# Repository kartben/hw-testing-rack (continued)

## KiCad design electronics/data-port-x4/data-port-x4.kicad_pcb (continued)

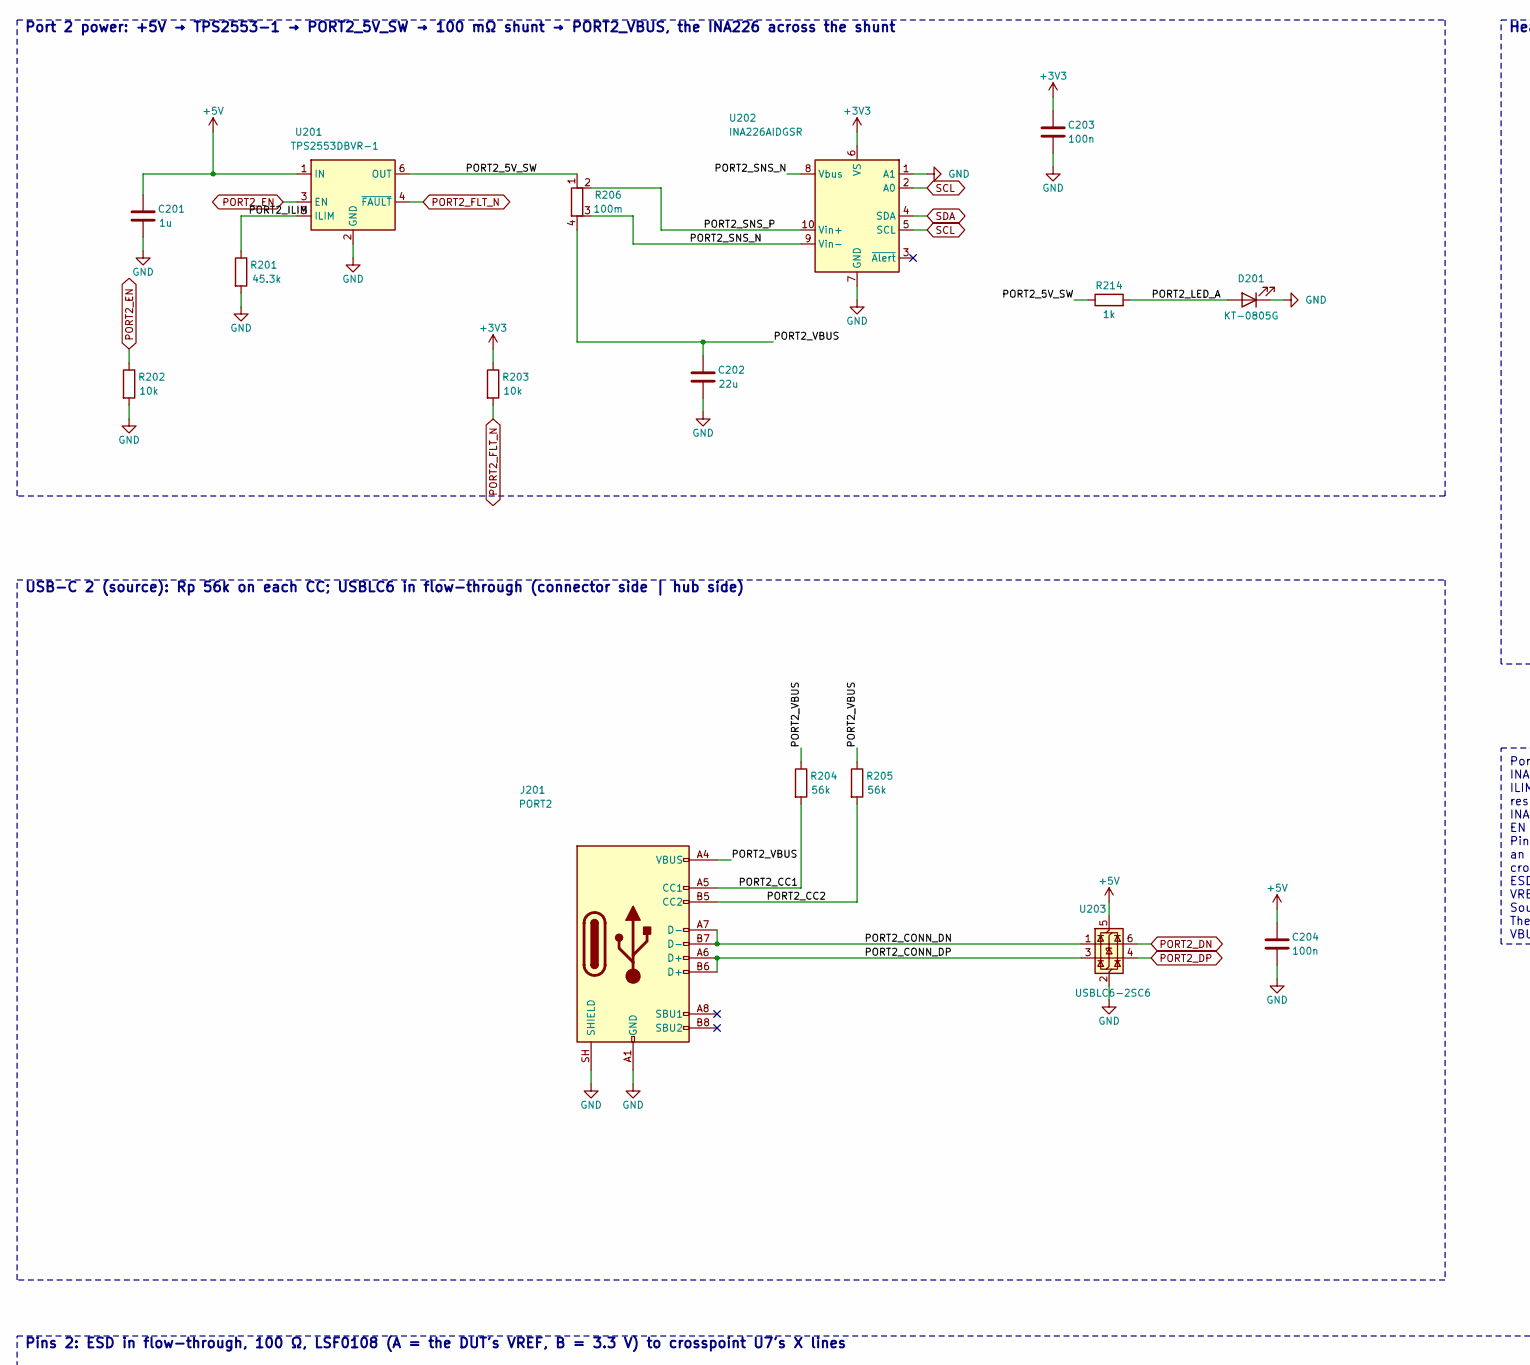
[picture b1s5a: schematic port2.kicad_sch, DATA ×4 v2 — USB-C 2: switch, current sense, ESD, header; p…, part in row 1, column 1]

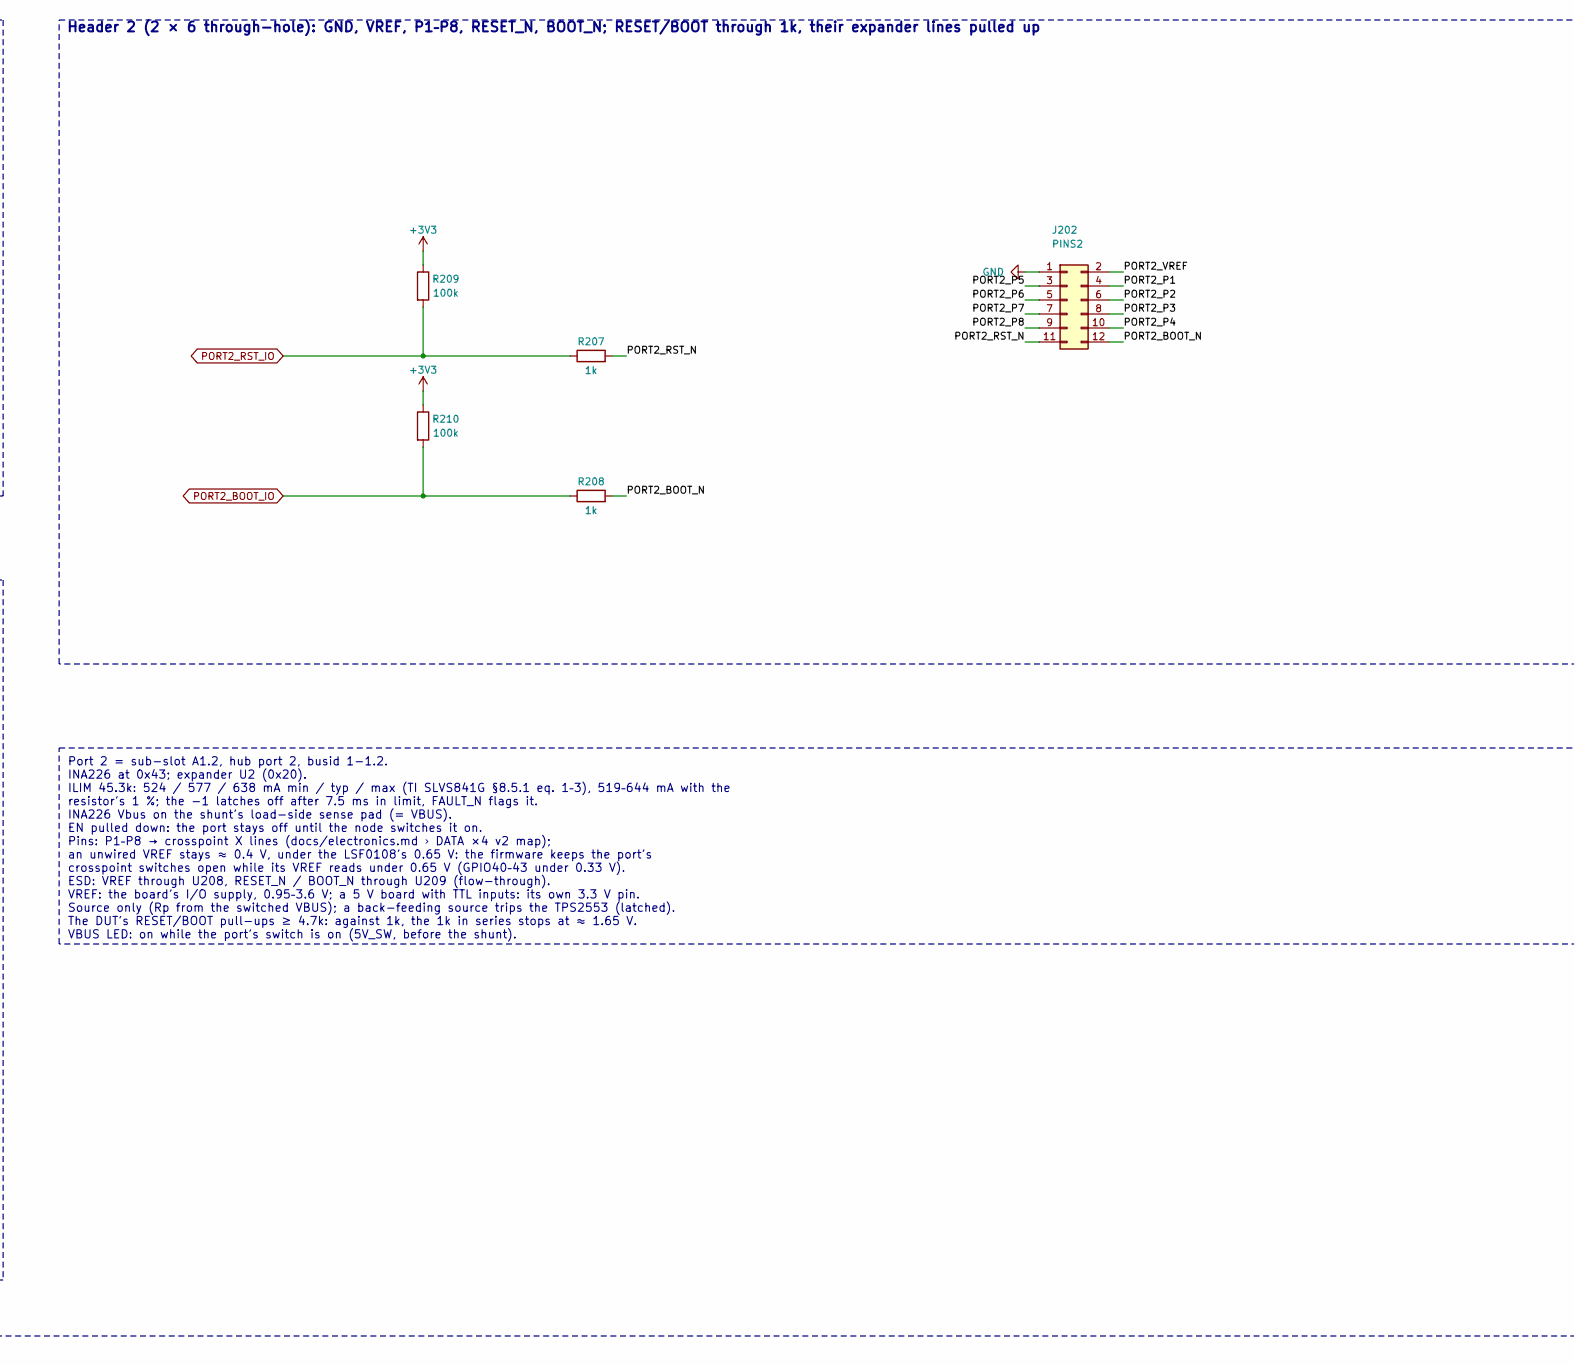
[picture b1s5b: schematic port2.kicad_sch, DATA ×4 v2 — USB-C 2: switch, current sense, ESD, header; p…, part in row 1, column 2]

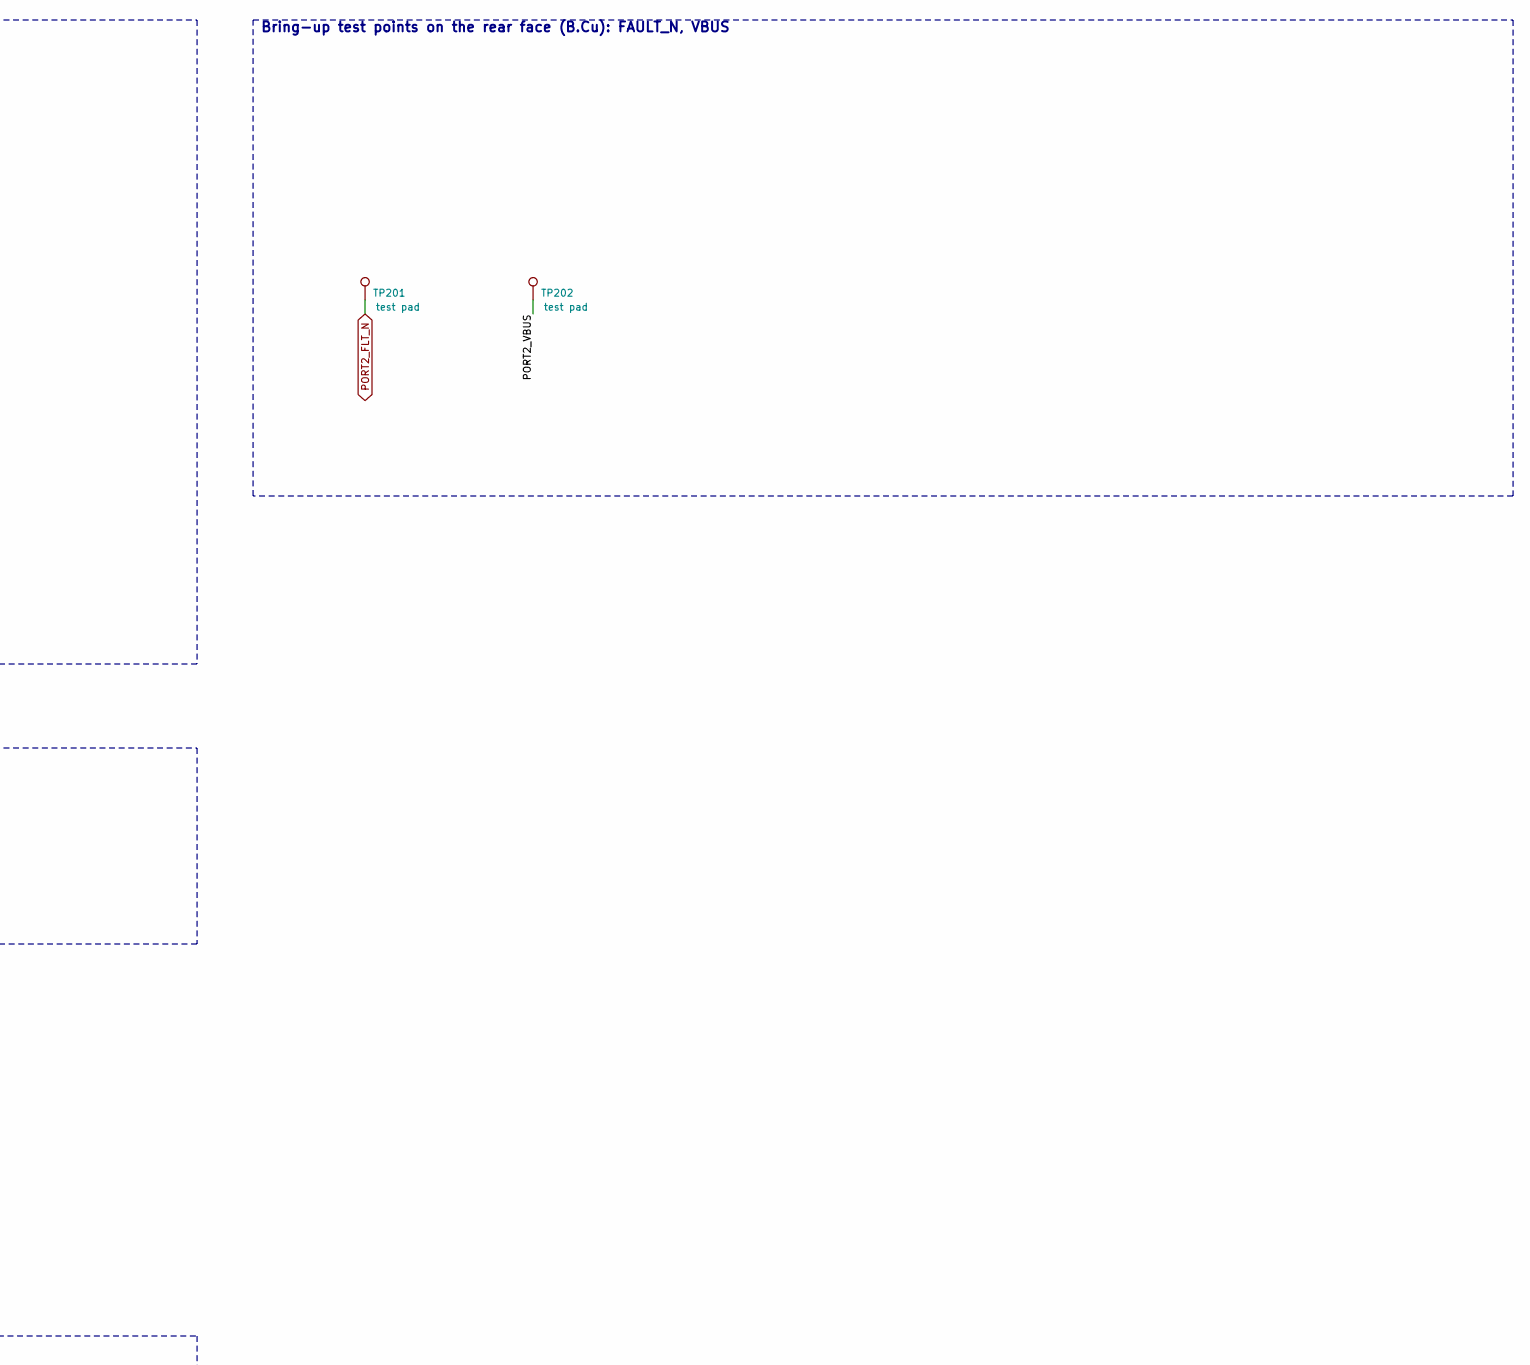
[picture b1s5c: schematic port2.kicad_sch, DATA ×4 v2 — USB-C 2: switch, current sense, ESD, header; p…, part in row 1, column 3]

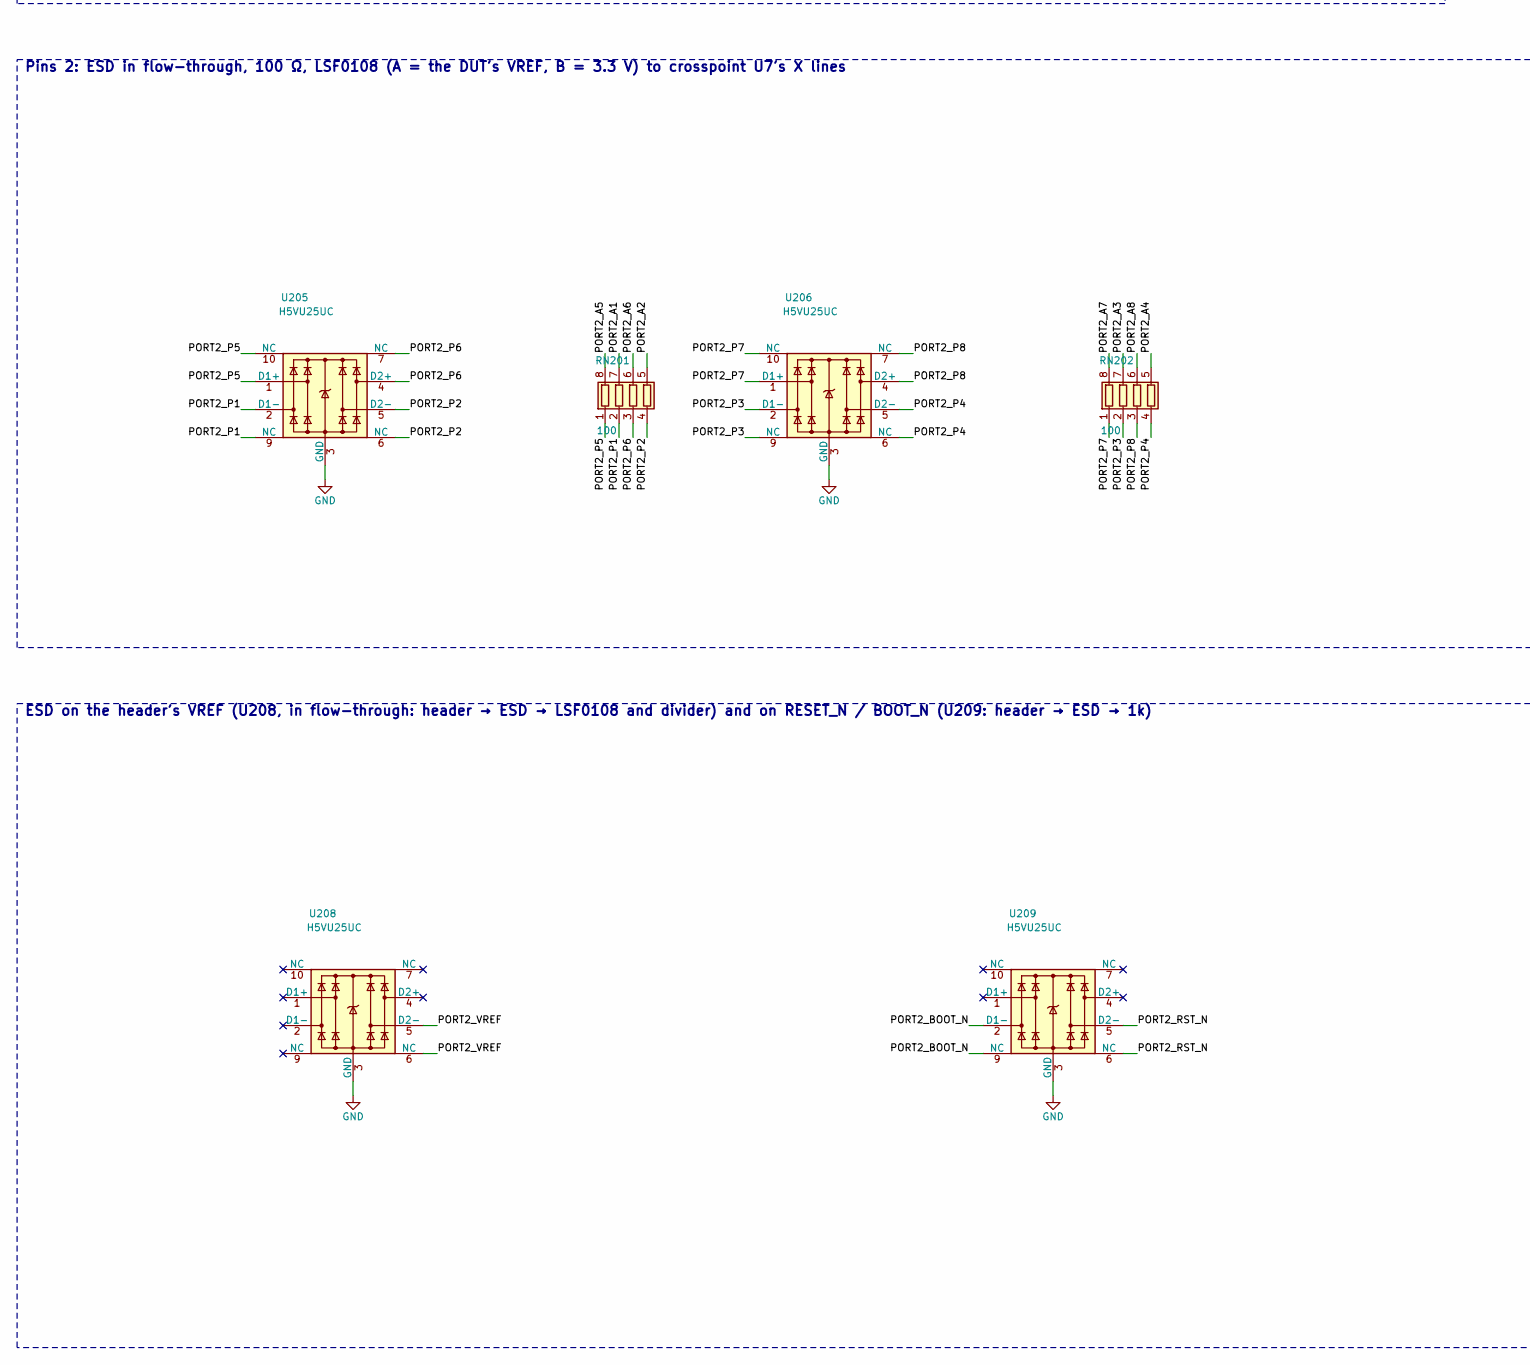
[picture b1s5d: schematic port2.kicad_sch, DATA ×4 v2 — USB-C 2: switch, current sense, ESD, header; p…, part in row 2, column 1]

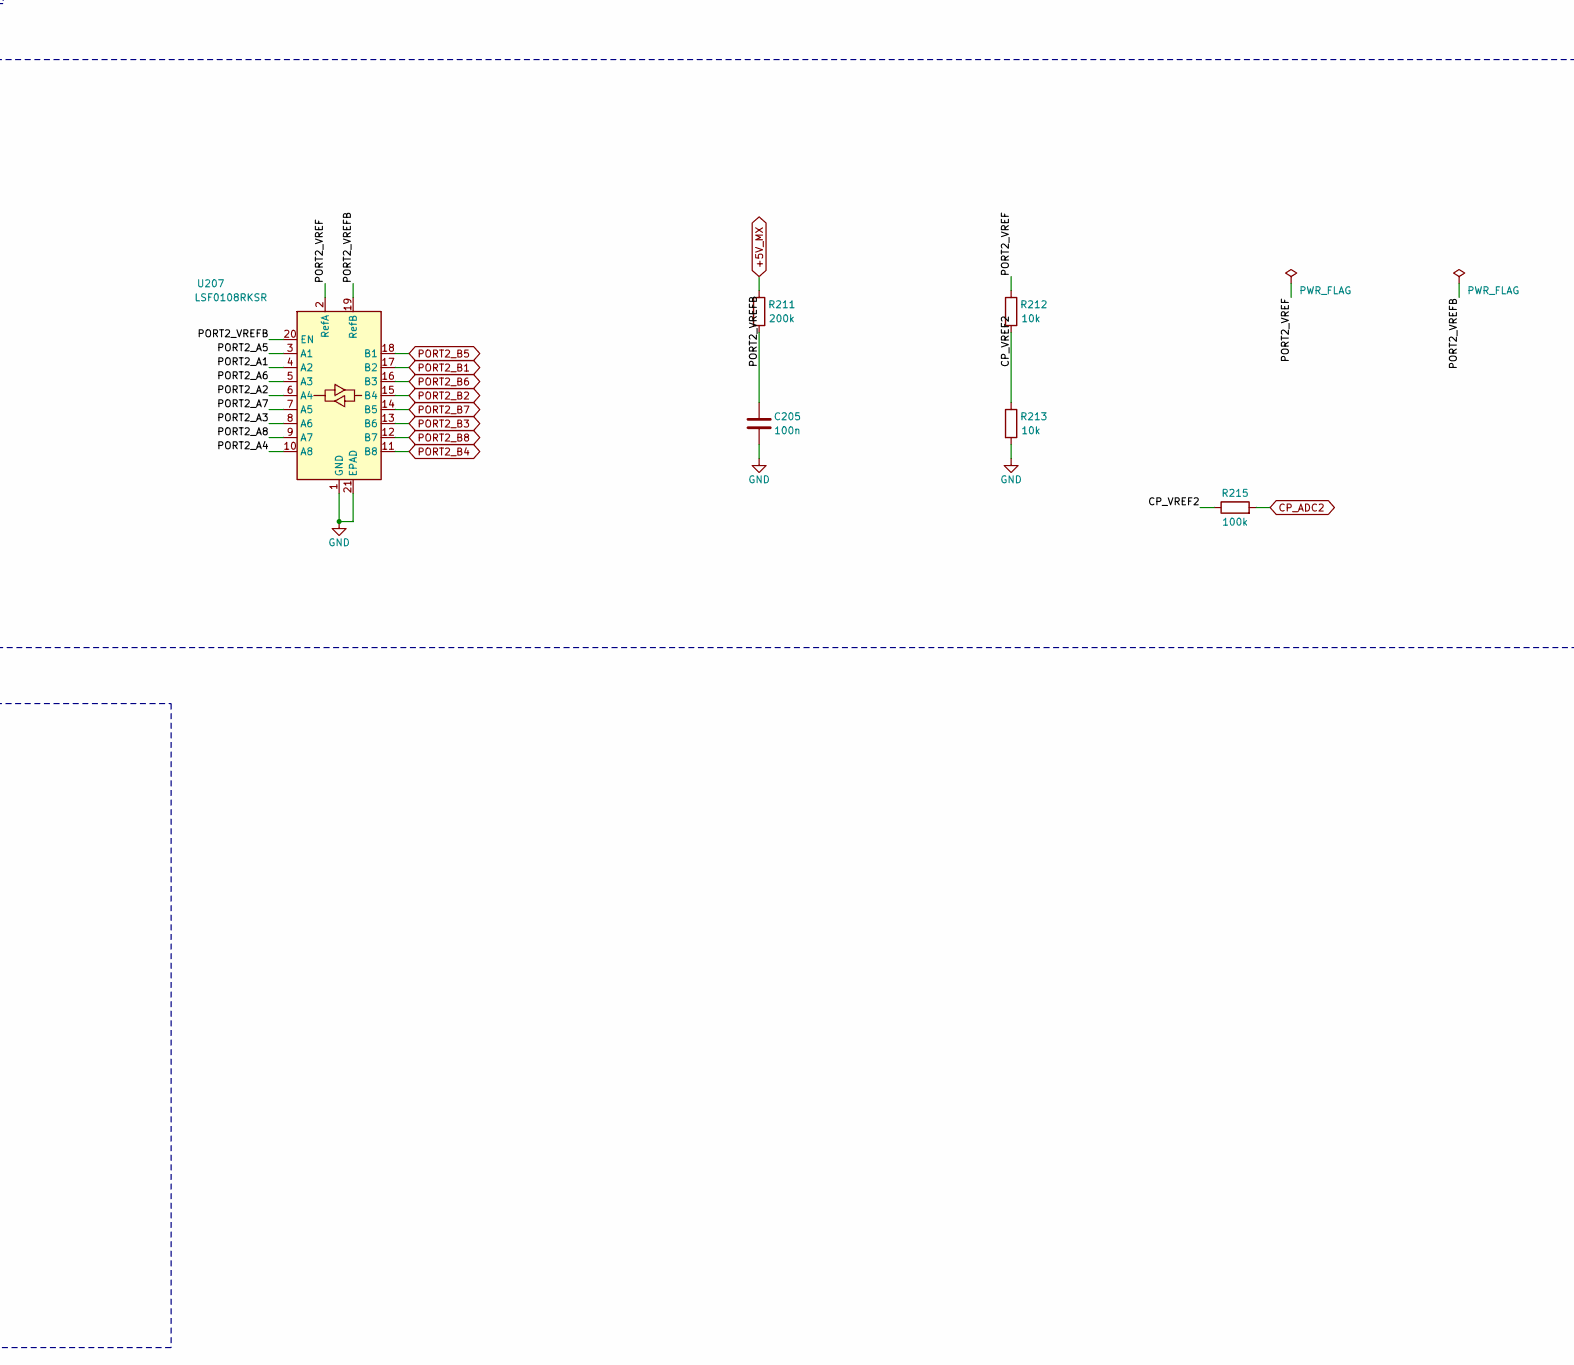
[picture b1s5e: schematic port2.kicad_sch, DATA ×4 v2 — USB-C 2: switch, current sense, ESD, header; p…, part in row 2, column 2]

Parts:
C201: 1u; C_0402_1005Metric; MPN CL05A105KA5NQNC; LCSC C52923
C202: 22u; C_0805_2012Metric; MPN CL21A226MAQNNNE; LCSC C45783
C203, C204, C205: 100n; C_0402_1005Metric; MPN CL05B104KO5NNNC; LCSC C1525
D201: KT-0805G; LED_0805_2012Metric; MPN KT-0805G; LCSC C2297
J201: PORT2; USB_C_Receptacle_GCT_USB4145-03-0170-C_Vertical; MPN USB4145-03-0170-C; LCSC C5181332
J202: PINS2; PinHeader_2x06_P2.54mm_Vertical; MPN HX PZ2.54-2x6P ZZ; LCSC C32713279
R201: 45.3k; R_0402_1005Metric; MPN FRC0402F4532TS; LCSC C2933099
R202, R203, R212, R213: 10k; R_0402_1005Metric; MPN 0402WGF1002TCE; LCSC C25744
R204, R205: 56k; R_0402_1005Metric; MPN 0402WGF5602TCE; LCSC C25796
R206: 100m; R_1206_3216Metric_Kelvin; MPN 1206W4F100LT5E; LCSC C25334
R207, R208, R214: 1k; R_0402_1005Metric; MPN 0402WGF1001TCE; LCSC C11702
R209, R210, R215: 100k; R_0402_1005Metric; MPN 0402WGF1003TCE; LCSC C25741
R211: 200k; R_0402_1005Metric; MPN 0402WGF2003TCE; LCSC C25764
RN201, RN202: 100; R_Array_Convex_4x0402; MPN 4D02WGJ0101TCE; LCSC C48442
TP201: test pad; TestPoint_Pad_D1.0mm; MPN test pad
TP202: test pad; TestPoint_Pad_D1.5mm; MPN test pad
U201: TPS2553DBVR-1; SOT-23-6; MPN TPS2553DBVR-1; LCSC C111738
U202: INA226AIDGSR; TSSOP-10_3x3mm_P0.5mm; MPN INA226AIDGSR; LCSC C49851
U203: USBLC6-2SC6; SOT-23-6; MPN USBLC6-2SC6; LCSC C7519
U205, U206, U208, U209: H5VU25UC; DFN2510-10L_2.5x1.0mm_P0.5mm; MPN H5VU25UC; LCSC C20615800
U207: LSF0108RKSR; DHVQFN-20-1EP_2.5x4.5mm_P0.5mm_EP1x3mm; MPN LSF0108RKSR; LCSC C130008

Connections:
+3V3: C203.1, R203.1, R209.1, R210.1, U202.6 (VS); also elsewhere on the board
+5V: C201.1, C204.1, U201.1 (IN), U203.5 (VBUS); also elsewhere on the board
+5V_MX: R211.1; also elsewhere on the board
/Port 2/CP_VREF2: R212.2, R213.1, R215.1
/Port 2/PORT2_5V_SW: R206.1, R214.1, U201.6 (OUT)
/Port 2/PORT2_A1: RN201.7 (R2.2), U207.4 (A2)
/Port 2/PORT2_A2: RN201.5 (R4.2), U207.6 (A4)
/Port 2/PORT2_A3: RN202.7 (R2.2), U207.8 (A6)
/Port 2/PORT2_A4: RN202.5 (R4.2), U207.10 (A8)
/Port 2/PORT2_A5: RN201.8 (R1.2), U207.3 (A1)
/Port 2/PORT2_A6: RN201.6 (R3.2), U207.5 (A3)
/Port 2/PORT2_A7: RN202.8 (R1.2), U207.7 (A5)
/Port 2/PORT2_A8: RN202.6 (R3.2), U207.9 (A7)
/Port 2/PORT2_BOOT_N: J202.12, R208.2, U209.2 (D1-), U209.9 (NC)
/Port 2/PORT2_CC1: J201.A5 (CC1), R204.2
/Port 2/PORT2_CC2: J201.B5 (CC2), R205.2
/Port 2/PORT2_CONN_DN: J201.A7 (D-), J201.B7 (D-), U203.1 (I/O1)
/Port 2/PORT2_CONN_DP: J201.A6 (D+), J201.B6 (D+), U203.3 (I/O2)
/Port 2/PORT2_ILIM: R201.1, U201.5 (ILIM)
/Port 2/PORT2_LED_A: D201.2 (A), R214.2
/Port 2/PORT2_P1: J202.4, RN201.2 (R2.1), U205.2 (D1-), U205.9 (NC)
/Port 2/PORT2_P2: J202.6, RN201.4 (R4.1), U205.5 (D2-), U205.6 (NC)
/Port 2/PORT2_P3: J202.8, RN202.2 (R2.1), U206.2 (D1-), U206.9 (NC)
/Port 2/PORT2_P4: J202.10, RN202.4 (R4.1), U206.5 (D2-), U206.6 (NC)
/Port 2/PORT2_P5: J202.3, RN201.1 (R1.1), U205.1 (D1+), U205.10 (NC)
/Port 2/PORT2_P6: J202.5, RN201.3 (R3.1), U205.4 (D2+), U205.7 (NC)
/Port 2/PORT2_P7: J202.7, RN202.1 (R1.1), U206.1 (D1+), U206.10 (NC)
/Port 2/PORT2_P8: J202.9, RN202.3 (R3.1), U206.4 (D2+), U206.7 (NC)
/Port 2/PORT2_RST_N: J202.11, R207.2, U209.5 (D2-), U209.6 (NC)
/Port 2/PORT2_SNS_N: R206.3, U202.8 (Vbus), U202.9 (Vin-)
/Port 2/PORT2_SNS_P: R206.2, U202.10 (Vin+)
/Port 2/PORT2_VBUS: C202.1, J201.A4 (VBUS), J201.A9 (VBUS), J201.B4 (VBUS), J201.B9 (VBUS), R204.1, R205.1, R206.4, TP202.1
/Port 2/PORT2_VREF: J202.2, R212.1, U207.2 (RefA), U208.5 (D2-), U208.6 (NC)
/Port 2/PORT2_VREFB: C205.1, R211.2, U207.19 (RefB), U207.20 (EN)
CP_ADC2: R215.2; also elsewhere on the board
GND: C201.2, C202.2, C203.2, C204.2, C205.2, D201.1 (K), J201.A1 (GND), J201.A12 (GND), J201.B1 (GND), J201.B12 (GND), J201.SH (SHIELD), J202.1, R201.2, R202.2, R213.2, U201.2 (GND), U202.1 (A1), U202.7 (GND), U203.2 (GND), U205.3 (GND), U205.8 (GND), U206.3 (GND), U206.8 (GND), U207.1 (GND), U207.21 (EPAD), U208.3 (GND), U208.8 (GND), U209.3 (GND), U209.8 (GND); also elsewhere on the board
PORT2_B1: U207.17 (B2); also elsewhere on the board
PORT2_B2: U207.15 (B4); also elsewhere on the board
PORT2_B3: U207.13 (B6); also elsewhere on the board
PORT2_B4: U207.11 (B8); also elsewhere on the board
PORT2_B5: U207.18 (B1); also elsewhere on the board
PORT2_B6: U207.16 (B3); also elsewhere on the board
PORT2_B7: U207.14 (B5); also elsewhere on the board
PORT2_B8: U207.12 (B7); also elsewhere on the board
PORT2_BOOT_IO: R208.1, R210.2; also elsewhere on the board
PORT2_DN: U203.6 (I/O1); also elsewhere on the board
PORT2_DP: U203.4 (I/O2); also elsewhere on the board
PORT2_EN: R202.1, U201.3 (EN); also elsewhere on the board
PORT2_FLT_N: R203.2, TP201.1, U201.4 (~FAULT); also elsewhere on the board
PORT2_RST_IO: R207.1, R209.2; also elsewhere on the board
SCL: U202.2 (A0), U202.5 (SCL); also elsewhere on the board
SDA: U202.4 (SDA); also elsewhere on the board

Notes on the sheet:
Port 2 power: +5V → TPS2553-1 → PORT2_5V_SW → 100 mΩ shunt → PORT2_VBUS, the INA226 across the shunt
Bring-up test points on the rear face (B.Cu): FAULT_N, VBUS
USB-C 2 (source): Rp 56k on each CC; USBLC6 in flow-through (connector side | hub side)
Header 2 (2 × 6 through-hole): GND, VREF, P1–P8, RESET_N, BOOT_N; RESET/BOOT through 1k, their expander lines pulled up
ESD on the header's VREF (U208, in flow-through: header → ESD → LSF0108 and divider) and on RESET_N / BOOT_N (U209: header → ESD → 1k)
Pins 2: ESD in flow-through, 100 Ω, LSF0108 (A = the DUT's VREF, B = 3.3 V) to crosspoint U7's X lines
Port 2 = sub-slot A1.2, hub port 2, busid 1-1.2. INA226 at 0x43; expander U2 (0x20). ILIM 45.3k: 524 / 577 / 638 mA min / typ / max (TI SLVS841G §8.5.1 eq. 1–3), 519–644 mA with the resistor's 1 %; the -1 latches off after 7.5 ms in limit, FAULT_N flags it. INA226 Vbus on the shunt's load-side sens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
